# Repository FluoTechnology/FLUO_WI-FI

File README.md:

## FLUO WI-FI

[*FLUO WI-FI (V01)*](http://fluotechnology.co.uk/product/fluo-wi-fi/)

The FLUO WI-FI is the best board to to create your own IoT solution. It is a microcontroller board based on the ATmega644p 
by ATMEL (MICROCHIP) that support Arduino Ecosystem and the ESP32 module by ESPRESSIF that enables Wi-Fi and Bluetooth Low Energy (BLE).

Repository Contents
-------------------
* **/Documentation** - Data sheets, Pinout, additional product information
* **/Hardware** - EAGLE design files (.brd, .sch)
* **/Production** - Gerber files
* **/Warranty&Declaration** - Declarations documents and warranty 

License Information
-------------------

This product is _**open source**_! 

Please review the LICENSE.md file for license information. 

If you have any questions or concerns on licensing, please contact support@fluotechnology.co.uk.

Distributed as-is; no warranty is given.

  *With* :heart: *from the FLUO Team.*

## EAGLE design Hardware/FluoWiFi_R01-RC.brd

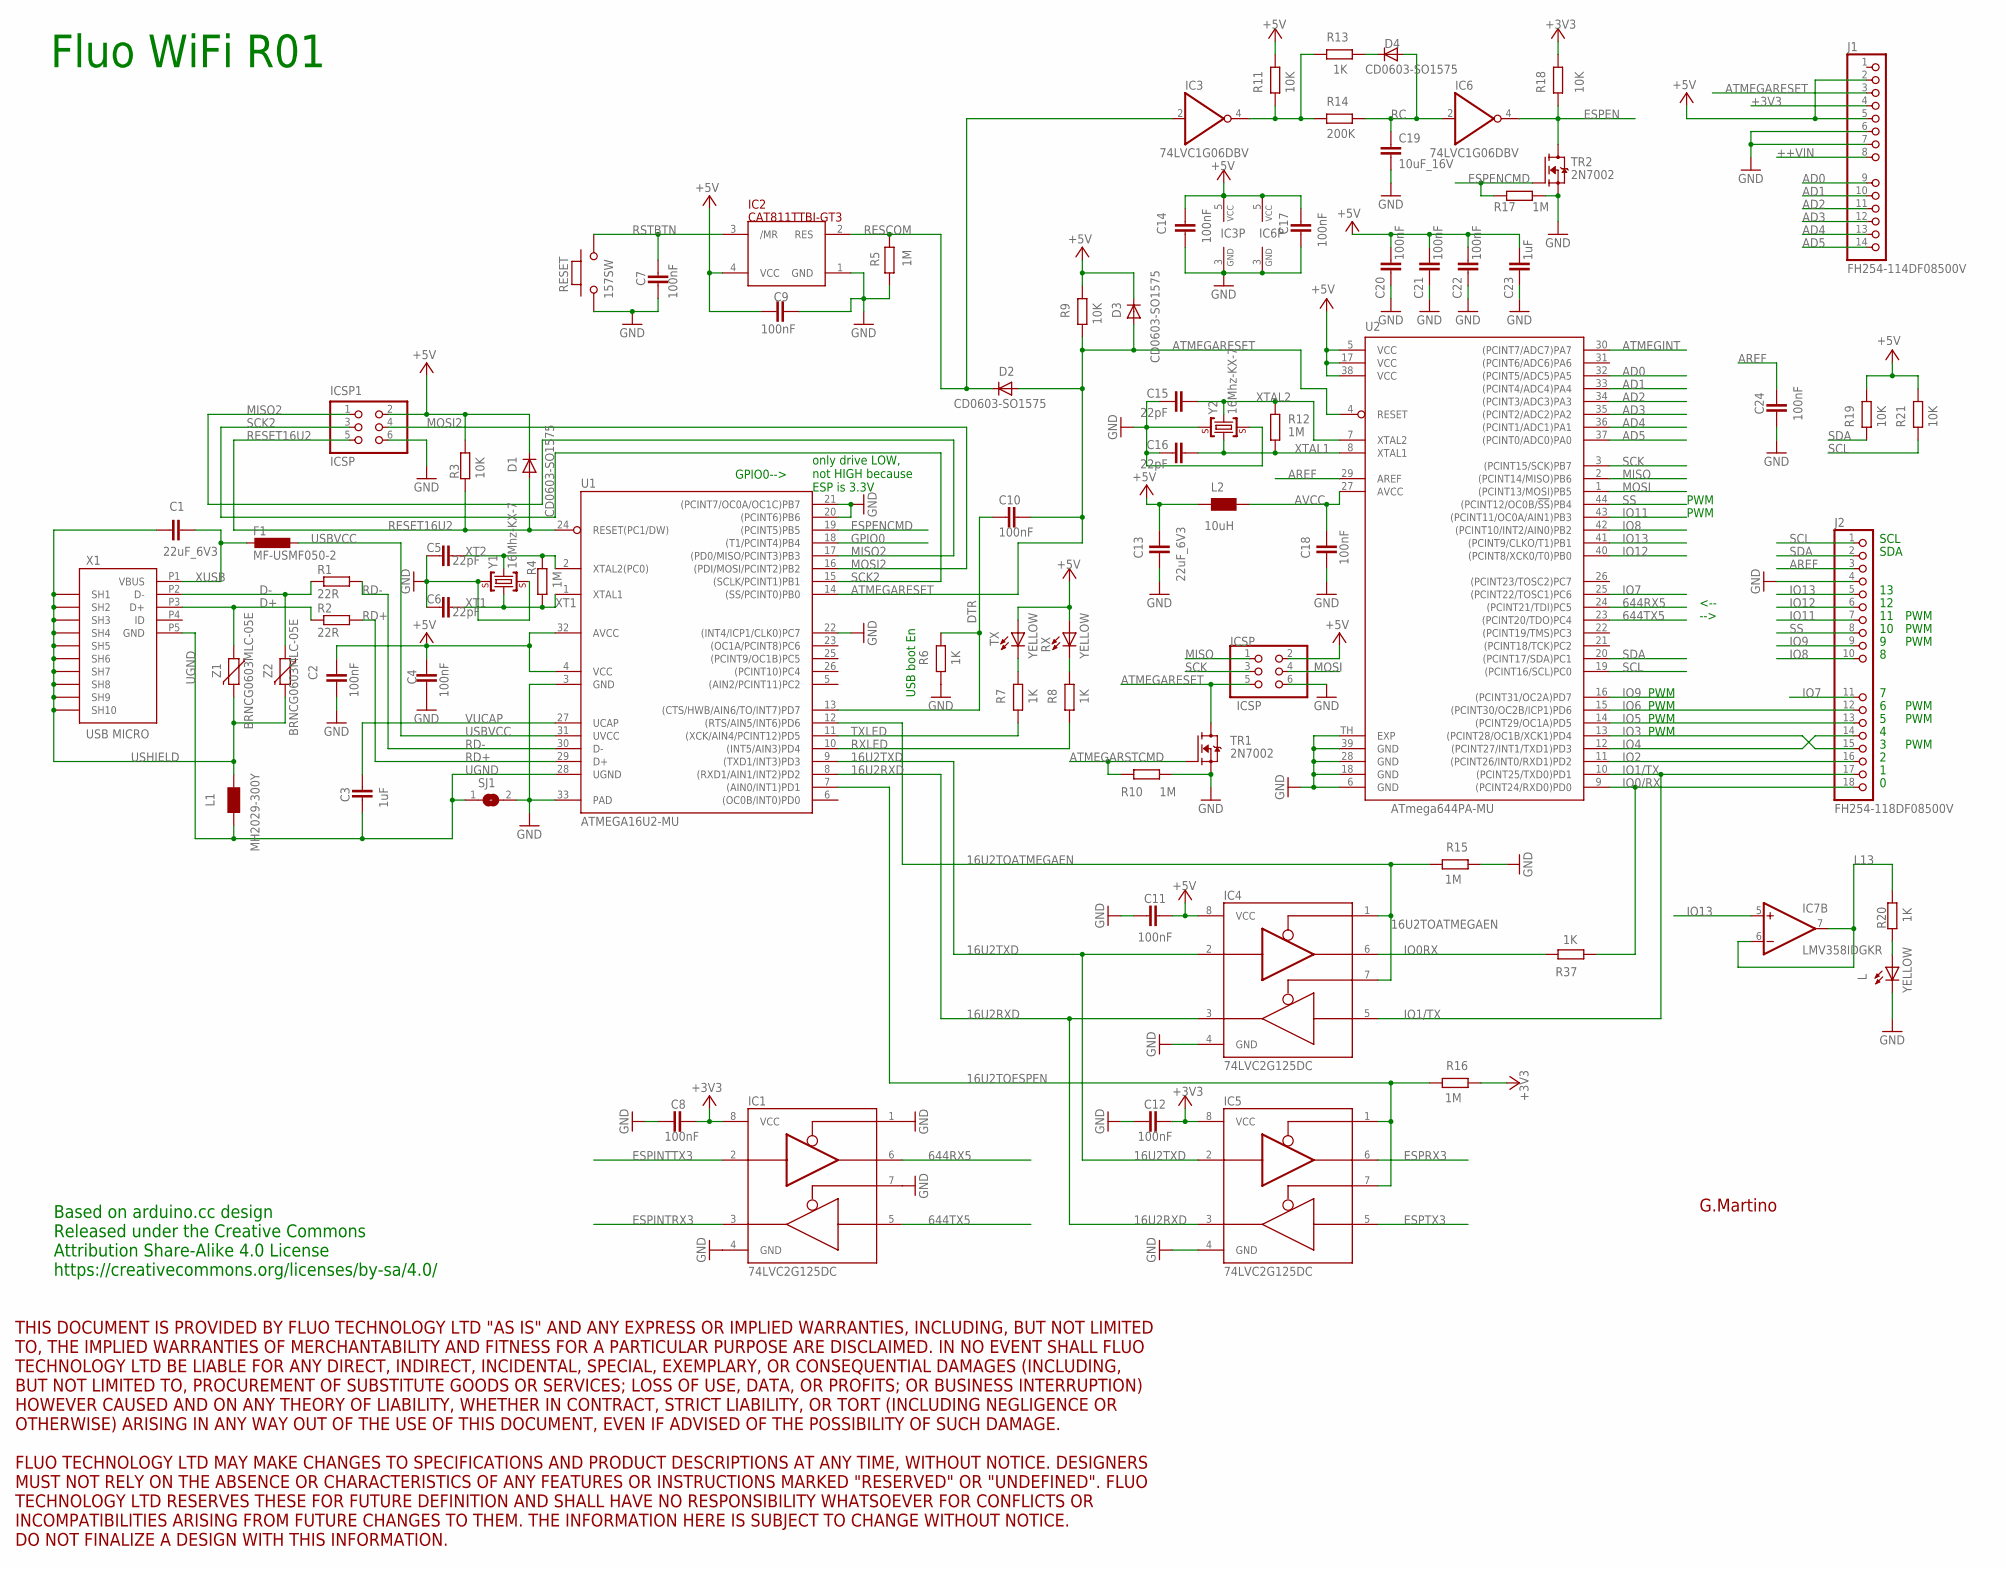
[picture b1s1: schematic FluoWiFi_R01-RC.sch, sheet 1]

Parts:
C1, C13: 22uF_6V3; C0603-ROUND
C2, C4, C7, C8, C9, C10, C11, C12, C14, C17, C18, C20, C21, C22, C24: 100nF; C0402
C3, C23: 1uF; C0402
C5, C6, C15, C16: 22pF; C0402
C19: 10uF_16V; C0805_ROUND
D1, D2, D3, D4: CD0603-SO1575; 0603
F1: MF-USMF050-2; 1210
IC1, IC4, IC5: 74LVC2G125DC; VSSOP8
IC2: CAT811TTBI-GT3; SOT143
IC3, IC6: 74LVC1G06DBV; SOT23-5
IC7: LMV358IDGKR; MSOP08
ICSP, ICSP1: ICSP; 2X03
J1: FH254-114DF08500V; 1-14-TH-PRESSFIT
J2: FH254-118DF08500V; 1X18-TH-PRESSFIT
L: YELLOW; 0402_CHIP_LED
L1: MH2029-300Y; 0805
L2: 10uH; 0805
R1, R2: 22R; R0402
R3, R9, R11, R18, R19, R21: 10K; R0402
R4, R5, R10, R12, R15, R16, R17: 1M; R0402
R6, R7, R8, R13, R20, R37: 1K; R0402
R14: 200K; R0402
RESET: 157SW; SMD_157SW
RX: YELLOW; 0402_CHIP_LED
SJ1: SJSJ_NO_RESIST; SJ_NO_RESIST
TR1, TR2: 2N7002; SOT-23
TX: YELLOW; 0402_CHIP_LED
U1: ATMEGA16U2-MU; MLF32
U2: ATmega644PA-MU; VQFN44
U$1: DISCLAIMER-FLUO
X1: USB MICRO; CON2_USB_MICRO_B_AT_HOLES
Y1, Y2: 16Mhz-KX-7; CRYSTAL-3.2-2.5
Z1, Z2: BRNCG0603MLC-05E; CT/CN0603

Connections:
16U2RXD: IC4.3 (2Y), IC5.3 (2Y), U1.8 ((RXD1/AIN1/INT2)PD2)
16U2TOATMEGAEN: IC4.1 (OE1), IC4.7 (OE2), R15.2, U1.12 ((RTS/AIN5/INT6)PD6)
16U2TOESPEN: IC5.1 (OE1), IC5.7 (OE2), R16.2, U1.7 ((AIN0/INT1)PD1)
16U2TXD: IC4.2 (1A), IC5.2 (1A), U1.9 ((TXD1/INT3)PD3)
644RX5: IC1.6 (1Y), U2.24 ((PCINT21/TDI)PC5)
644TX5: IC1.5 (2A), U2.23 ((PCINT20/TDO)PC4)
+3V3: C8.2, C12.1, IC1.8 (VCC), IC5.8 (VCC), J1.4, R16.1, R18.2; also elsewhere on the board
+5V: C2.1, C4.2, C9.1, C11.1, C13.2, C14.2, C17.2, C20.2, C21.2, C22.2, C23.1, D1.C, D3.C, IC2.4 (VCC), IC3.5 (VCC), IC4.8 (VCC), IC6.5 (VCC), ICSP.2, ICSP1.2, J1.2, J1.5, L2.1, R3.2, R9.2, R11.2, R19.2, R21.2, RX.A, TX.A, U1.4 (VCC), U1.32 (AVCC), U2.5 (VCC), U2.17 (VCC), U2.38 (VCC); also elsewhere on the board
++VIN: J1.8; also elsewhere on the board
AD0: J1.9, U2.32 ((PCINT5/ADC5)PA5)
AD1: J1.10, U2.33 ((PCINT4/ADC4)PA4)
AD2: J1.11, U2.34 ((PCINT3/ADC3)PA3)
AD3: J1.12, U2.35 ((PCINT2/ADC2)PA2)
AD4: J1.13, U2.36 ((PCINT1/ADC1)PA1)
AD5: J1.14, U2.37 ((PCINT0/ADC0)PA0)
AREF: C24.2, J2.3, U2.29 (AREF)
ATMEGARESET: C10.2, D2.A, D3.A, ICSP.5, J1.3, R9.1, TR1.3 (D), U1.14 ((SS/PCINT0)PB0), U2.4 (RESET)
ATMEGARSTCMD: R10.1, TR1.1 (G); also elsewhere on the board
ATMEGINT: U2.30 ((PCINT7/ADC7)PA7); also elsewhere on the board
AVCC: C18.2, L2.2, U2.27 (AVCC)
D+: R2.1, X1.P3 (D+), Z1.1
D-: R1.1, X1.P2 (D-), Z2.1
DTR: C10.1, R6.2, U1.13 ((CTS/HWB/AIN6/TO/INT7)PD7)
ESPEN: IC6.4 (O), R18.1, TR2.3 (D); also elsewhere on the board
ESPENCMD: R17.1, TR2.1 (G), U1.19 ((PCINT5)PB5)
ESPINTRX3: IC1.3 (2Y); also elsewhere on the board
ESPINTTX3: IC1.2 (1A); also elsewhere on the board
ESPRX3: IC5.6 (1Y); also elsewhere on the board
ESPTX3: IC5.5 (2A); also elsewhere on the board
GND: C2.2, C4.1, C5.2, C6.2, C7.1, C8.1, C9.2, C11.2, C12.2, C13.1, C14.1, C15.2, C16.2, C17.1, C18.1, C19.2, C20.1, C21.1, C22.1, C23.2, C24.1, IC1.1 (OE1), IC1.4 (GND), IC1.7 (OE2), IC2.1 (GND), IC3.3 (GND), IC4.4 (GND), IC5.4 (GND), IC6.3 (GND), ICSP.6, ICSP1.6, J1.6, J1.7, J2.4, L.C, R5.1, R6.1, R10.2, R15.1, R17.2, RESET.1, SJ1.2, TR1.2 (S), TR2.2 (S), U1.3 (GND), U1.20 ((PCINT6)PB6), U1.21 ((PCINT7/OC0A/OC1C)PB7), U1.22 ((INT4/ICP1/CLK0)PC7), U1.33 (PAD), U2.6 (GND), U2.18 (GND), U2.28 (GND), U2.39 (GND), U2.TH (EXP), Y1.2 (GND), Y1.4 (GND), Y2.2 (GND), Y2.4 (GND); also elsewhere on the board
GPIO0: U1.18 ((T1/PCINT4)PB4); also elsewhere on the board
IO0/RX: J2.18, R37.1, U2.9 ((PCINT24/RXD0)PD0)
IO0RX: IC4.6 (1Y), R37.2
IO1/TX: IC4.5 (2A), J2.17, U2.10 ((PCINT25/TXD0)PD1)
IO2: J2.16, U2.11 ((PCINT26/INT0/RXD1)PD2)
IO3: J2.15, U2.13 ((PCINT28/OC1B/XCK1)PD4)
IO4: J2.14, U2.12 ((PCINT27/INT1/TXD1)PD3)
IO5: J2.13, U2.14 ((PCINT29/OC1A)PD5)
IO6: J2.12, U2.15 ((PCINT30/OC2B/ICP1)PD6)
IO7: J2.11, U2.25 ((PCINT22/TOSC1)PC6)
IO8: J2.10, U2.42 ((PCINT10/INT2/AIN0)PB2)
IO9: J2.9, U2.16 ((PCINT31/OC2A)PD7)
IO11: J2.7, U2.43 ((PCINT11/OC0A/AIN1)PB3)
IO12: J2.6, U2.40 ((PCINT8/XCK0/T0)PB0)
IO13: IC7.5 (+IN), J2.5, U2.41 ((PCINT9/CLKO/T1)PB1)
L13: IC7.6 (-IN), IC7.7 (OUT), R20.2
MISO: ICSP.1, U2.2 ((PCINT14/MISO)PB6); also elsewhere on the board
MISO2: ICSP1.1, U1.17 ((PD0/MISO/PCINT3)PB3)
MOSI: ICSP.4, U2.1 ((PCINT13/MOSI)PB5); also elsewhere on the board
MOSI2: ICSP1.4, U1.16 ((PDI/MOSI/PCINT2)PB2)
unnamed: IC3.4 (O), R11.1, R13.1, R14.2
unnamed: D4.C, R13.2
unnamed: R7.2, TX.C
unnamed: R8.2, RX.C
unnamed: L.A, R20.1
RC: C19.1, D4.A, IC6.2 (I), R14.1
RD+: R2.2, U1.29 (D+)
RD-: R1.2, U1.30 (D-)
RESCOM: D2.C, IC2.2 (RES), IC3.2 (I), R5.2
RESET16U2: D1.A, ICSP1.5, R3.1, U1.24 (RESET(PC1/DW))
RSTBTN: C7.2, IC2.3 (/MR), RESET.2
RXLED: R8.1, U1.10 ((INT5/AIN3)PD4)
SCK: ICSP.3, U2.3 ((PCINT15/SCK)PB7); also elsewhere on the board
SCK2: ICSP1.3, U1.15 ((SCLK/PCINT1)PB1)
SCL: J2.1, R21.1, U2.19 ((PCINT16/SCL)PC0)
SDA: J2.2, R19.1, U2.20 ((PCINT17/SDA)PC1)
SS: J2.8, U2.44 ((PCINT12/OC0B/!SS!)PB4)
TXLED: R7.1, U1.11 ((XCK/AIN4/PCINT12)PD5)
UGND: C3.2, L1.1, SJ1.1, U1.28 (UGND), X1.P5 (GND)
USBVCC: F1.1, U1.31 (UVCC); also elsewhere on the board
USHIELD: C1.2, L1.2, X1.P$2 (SH7), X1.P$3 (SH8), X1.P$6 (SH9), X1.P$7 (SH10), X1.S1 (SH1), X1.S2 (SH2), X1.S3 (SH3), X1.S4 (SH4), X1.S5 (SH5), X1.S6 (SH6), Z1.2, Z2.2
VUCAP: C3.1, U1.27 (UCAP)
XT1: C6.1, R4.1, U1.1 (XTAL1), Y1.1 (C1)
XT2: C5.1, R4.2, U1.2 (XTAL2(PC0)), Y1.3 (C2)
XTAL1: C16.1, R12.1, U2.8 (XTAL1), Y2.1 (C1)
XTAL2: C15.1, R12.2, U2.7 (XTAL2), Y2.3 (C2)
XUSB: C1.1, F1.2, X1.P1 (VBUS)

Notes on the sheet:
Fluo WiFi R01
USB boot En
SDA
SCL
G.Martino
PWM
-->
<--
only drive LOW, not HIGH because ESP is 3.3V
GPIO0-->
Based on arduino.cc design Released under the Creative Commons Attribution Share-Alike 4.0 License https://creativecommons.org/licenses/by-sa/4.0/

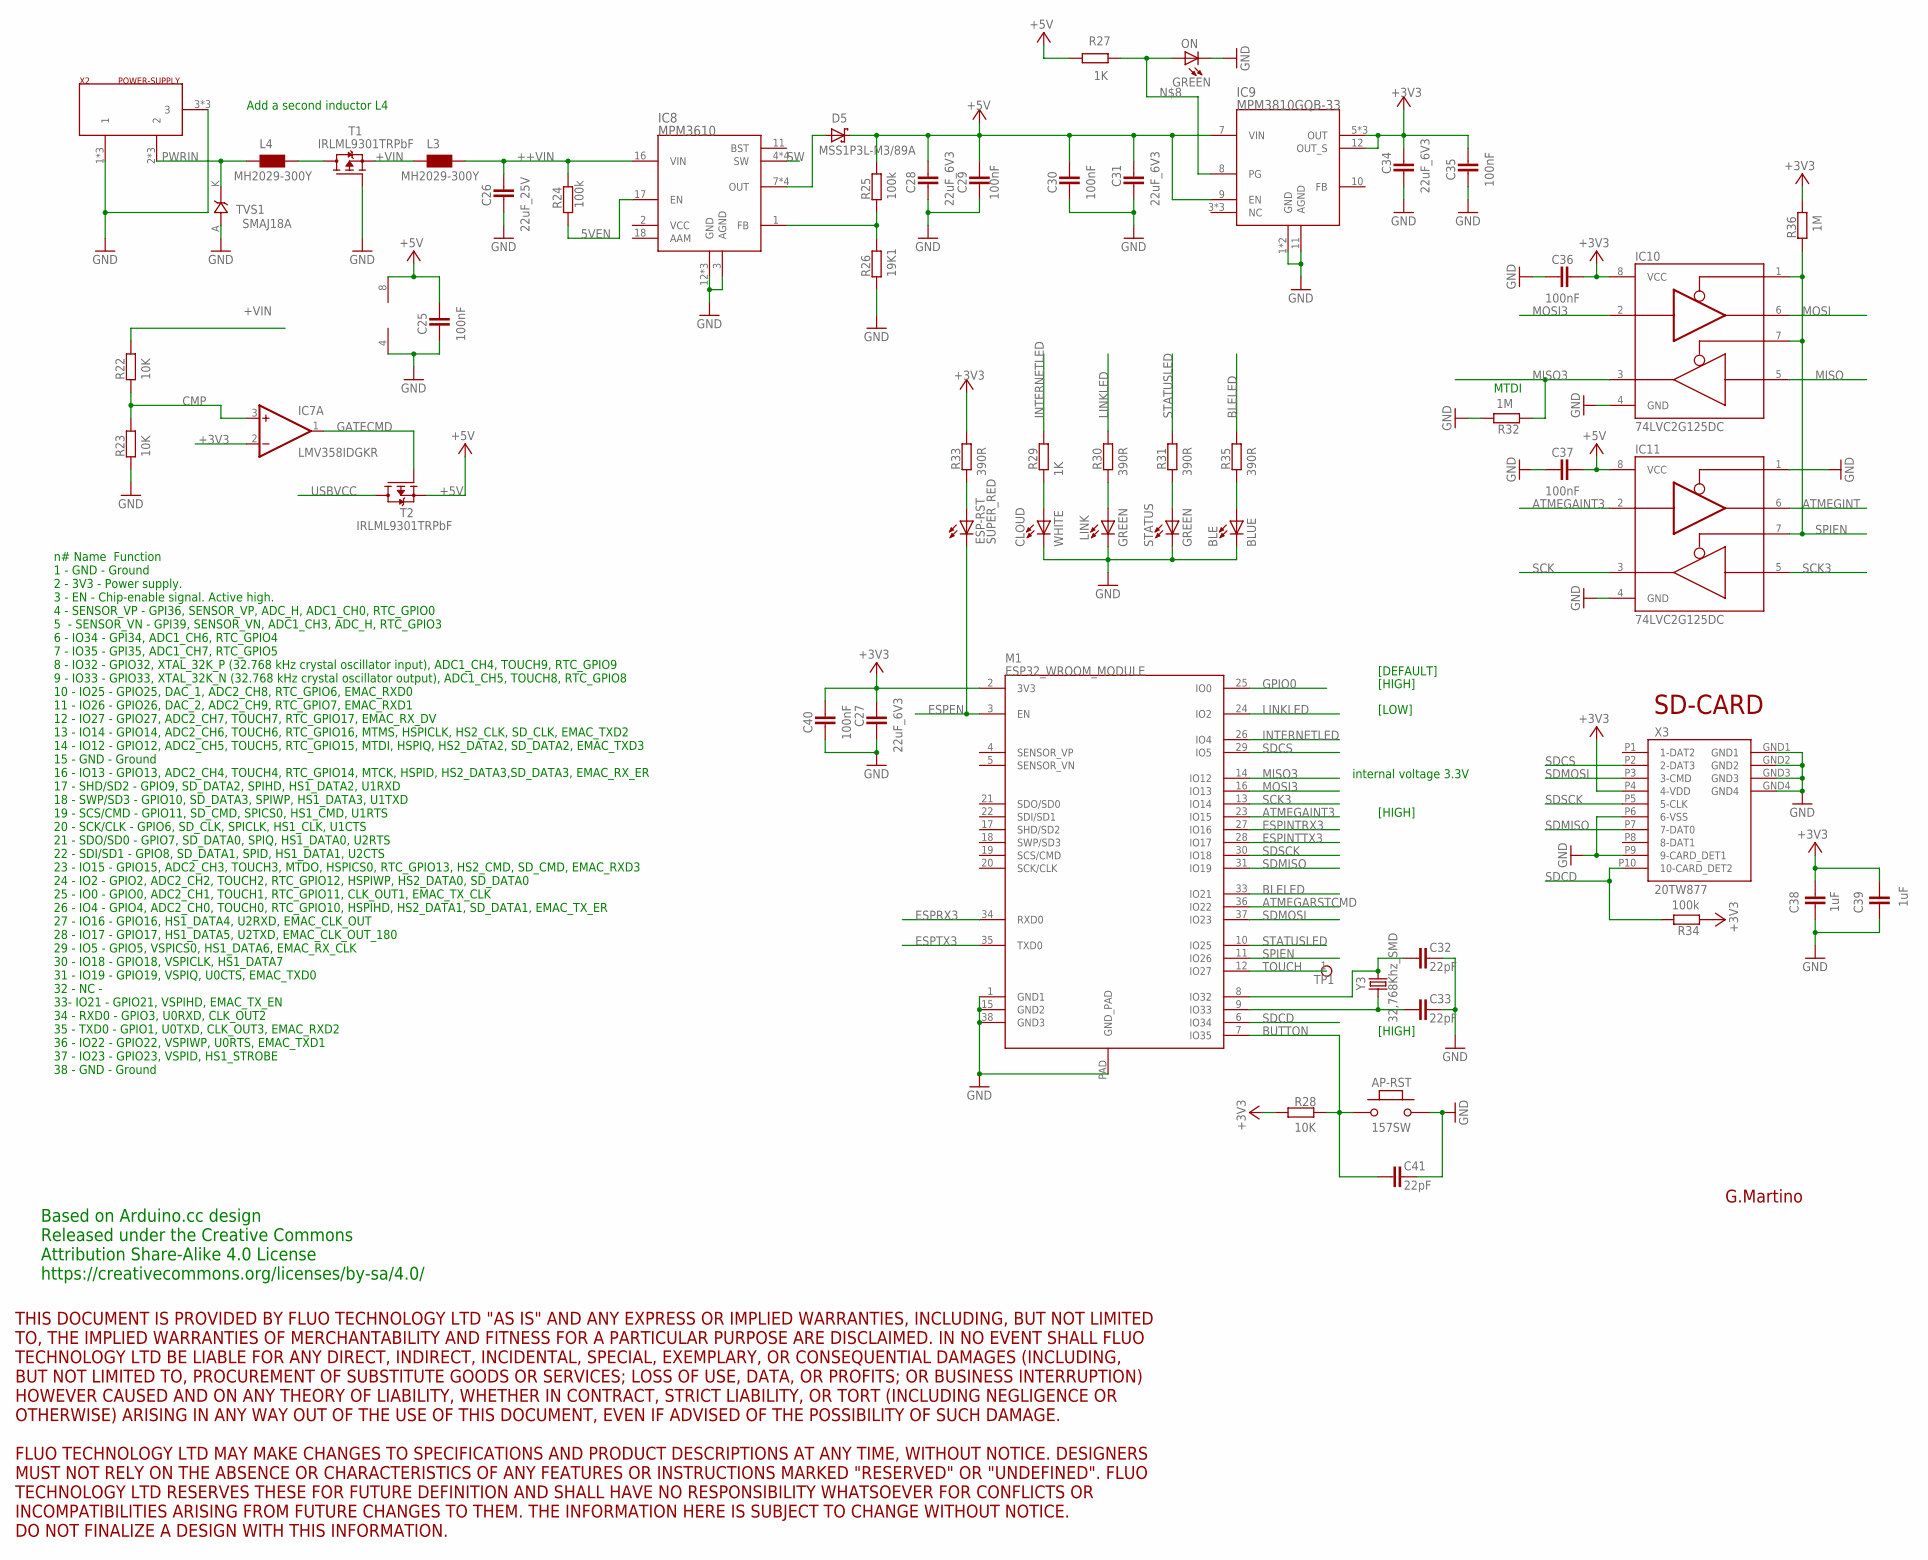
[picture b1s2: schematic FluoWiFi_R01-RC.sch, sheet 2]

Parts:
AP-RST: 157SW; SMD_157SW
BLE: BLUE; 0402_CHIP_LED
C25, C29, C30, C35, C36, C37, C40: 100nF; C0402
C26: 22uF_25V; C0805_ROUND
C27, C28, C31, C34: 22uF_6V3; C0603-ROUND
C32, C33, C41: 22pF; C0402
C38, C39: 1uF; C0402
CLOUD: WHITE; 0402_CHIP_LED
D5: MSS1P3L-M3/89A; MICROSMP
ESP-RST: SUPER_RED; 0402_CHIP_LED
IC7: LMV358IDGKR; MSOP08
IC8: MPM3610; QFN-20
IC9: MPM3810GQB-33; QFN-12
IC10, IC11: 74LVC2G125DC; VSSOP8
L3, L4: MH2029-300Y; 0805
LINK: GREEN; 0402_CHIP_LED
M1: ESP32_WROOM_MODULE; WROOM_ESP32
ON: GREEN; 0402_CHIP_LED
R22, R23, R28: 10K; R0402
R24, R25, R34: 100k; R0402
R26: 19K1; R0402
R27, R29: 1K; R0402
R30, R31, R33, R35: 390R; R0402
R32, R36: 1M; R0402
STATUS: GREEN; 0402_CHIP_LED
T1, T2: IRLML9301TRPbF; SOT-23
TP1: XXXX_TEST-POINTS_50; TEST_50
TVS1: SMAJ18A; SMA-TVS
U$2: DISCLAIMER-FLUO
X2: POWER-SUPPLY; POWERSUPPLY_DC-21MM
X3: 20TW877; 20TW877_CARD_CONNECTOR
Y3: 32,768Khz_SMD; RESONATOR_EPSON_FC_145

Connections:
5VEN: IC8.17 (EN), R24.2
+3V3: C27.1, C34.1, C35.2, C36.1, C38.2, C39.2, C40.2, IC7.2 (-IN), IC9.5 (OUT), IC9.6 (OUT), IC9.12 (OUT_S), IC9.14 (OUT), IC10.8 (VCC), M1.2 (3V3), R28.2, R33.2, R34.1, R36.1, X3.P4 (4-VDD); also elsewhere on the board
+5V: C25.2, C28.1, C29.1, C30.1, C31.1, C37.1, D5.K (C), IC7.8 (V+), IC9.7 (VIN), IC9.9 (EN), IC11.8 (VCC), R25.2, R27.2, T2.2 (S); also elsewhere on the board
+5V_SEZ: D5.A, IC8.7 (OUT), IC8.8 (OUT), IC8.9 (OUT), IC8.20 (OUT)
++VIN: C26.1, IC8.16 (VIN), L3.2, R24.1; also elsewhere on the board
+VIN: L3.1, R22.2, T1.2 (S)
ATMEGAINT3: IC11.2 (1A), M1.23 (IO15)
ATMEGARSTCMD: M1.36 (IO22); also elsewhere on the board
ATMEGINT: IC11.6 (1Y); also elsewhere on the board
BLELED: M1.33 (IO21), R35.2
BUTTON: AP-RST.1, C41.1, M1.7 (IO35), R28.1
CMP: IC7.3 (+IN), R22.1, R23.2
ESPEN: ESP-RST.C, M1.3 (EN); also elsewhere on the board
ESPINTRX3: M1.27 (IO16); also elsewhere on the board
ESPINTTX3: M1.28 (IO17); also elsewhere on the board
ESPRX3: M1.34 (RXD0); also elsewhere on the board
ESPTX3: M1.35 (TXD0); also elsewhere on the board
GATECMD: IC7.1 (OUT), T2.1 (G)
GND: AP-RST.2, BLE.C, C25.1, C26.2, C27.2, C28.2, C29.2, C30.2, C31.2, C32.2, C33.2, C34.2, C35.1, C36.2, C37.2, C38.1, C39.1, C40.1, C41.2, CLOUD.C, IC7.4 (V-), IC8.3 (AGND), IC8.12 (GND), IC8.13 (GND), IC8.14 (GND), IC9.1 (GND), IC9.2 (GND), IC9.11 (AGND), IC10.4 (GND), IC11.1 (OE1), IC11.4 (GND), LINK.C, M1.1 (GND1), M1.15 (GND2), M1.38 (GND3), M1.PAD (GND_PAD), ON.C, R23.1, R26.1, R32.1, STATUS.C, T1.1 (G), TVS1.A, X2.1, X2.3, X2.4 (1), X2.5 (1), X2.6 (3), X2.7 (3), X3.GND1, X3.GND2, X3.GND3, X3.GND4, X3.P6 (6-VSS), X3.P9 (9-CARD_DET1); also elsewhere on the board
GPIO0: M1.25 (IO0); also elsewhere on the board
INTERNETLED: M1.26 (IO4), R29.2
LINKLED: M1.24 (IO2), R30.2
MISO: IC10.5 (2A); also elsewhere on the board
MISO3: IC10.3 (2Y), M1.14 (IO12), R32.2
MOSI: IC10.6 (1Y); also elsewhere on the board
MOSI3: IC10.2 (1A), M1.16 (IO13)
unnamed: ESP-RST.A, R33.1
unnamed: L4.2, T1.3 (D)
unnamed: BLE.A, R35.1
unnamed: CLOUD.A, R29.1
unnamed: IC9.8 (PG), ON.A, R27.1
unnamed: C32.1, M1.8 (IO32), Y3.P$2 (2)
unnamed: C33.1, M1.9 (IO33), Y3.P$1 (1)
unnamed: LINK.A, R30.1
unnamed: R31.1, STATUS.A
unnamed: IC8.1 (FB), R25.1, R26.2
PWRIN: L4.1, TVS1.K, X2.2, X2.8 (2), X2.9 (2)
SCK: IC11.3 (2Y); also elsewhere on the board
SCK3: IC11.5 (2A), M1.13 (IO14)
SDCD: M1.6 (IO34), R34.2, X3.P10 (10-CARD_DET2)
SDCS: M1.29 (IO5), X3.P2 (2-DAT3)
SDMISO: M1.31 (IO19), X3.P7 (7-DAT0)
SDMOSI: M1.37 (IO23), X3.P3 (3-CMD)
SDSCK: M1.30 (IO18), X3.P5 (5-CLK)
SPIEN: IC10.1 (OE1), IC10.7 (OE2), IC11.7 (OE2), M1.11 (IO26), R36.2
STATUSLED: M1.10 (IO25), R31.2
SW: IC8.4 (SW), IC8.5 (SW), IC8.6 (SW), IC8.19 (SW)
TOUCH: M1.12 (IO27), TP1.1
USBVCC: T2.3 (D); also elsewhere on the board

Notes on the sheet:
n# Name Function 1 - GND - Ground 2 - 3V3 - Power supply. 3 - EN - Chip-enable signal. Active high. 4 - SENSOR_VP - GPI36, SENSOR_VP, ADC_H, ADC1_CH0, RTC_GPIO0 5 - SENSOR_VN - GPI39, SENSOR_VN, ADC1_CH3, ADC_H, RTC_GPIO3 6 - IO34 - GPI34, ADC1_CH6, RTC_GPIO4 7 - IO35 - GPI35, ADC1_CH7, RTC_GPIO5 8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
SD-CARD
MTDI
[HIGH]
[LOW]
internal voltage 3.3V
G.Martino
[DEFAULT]
Add a second inductor L4
Based on Arduino.cc design Released under the Creative Commons Attribution Share-Alike 4.0 License https://creativecommons.org/licenses/by-sa/4.0/

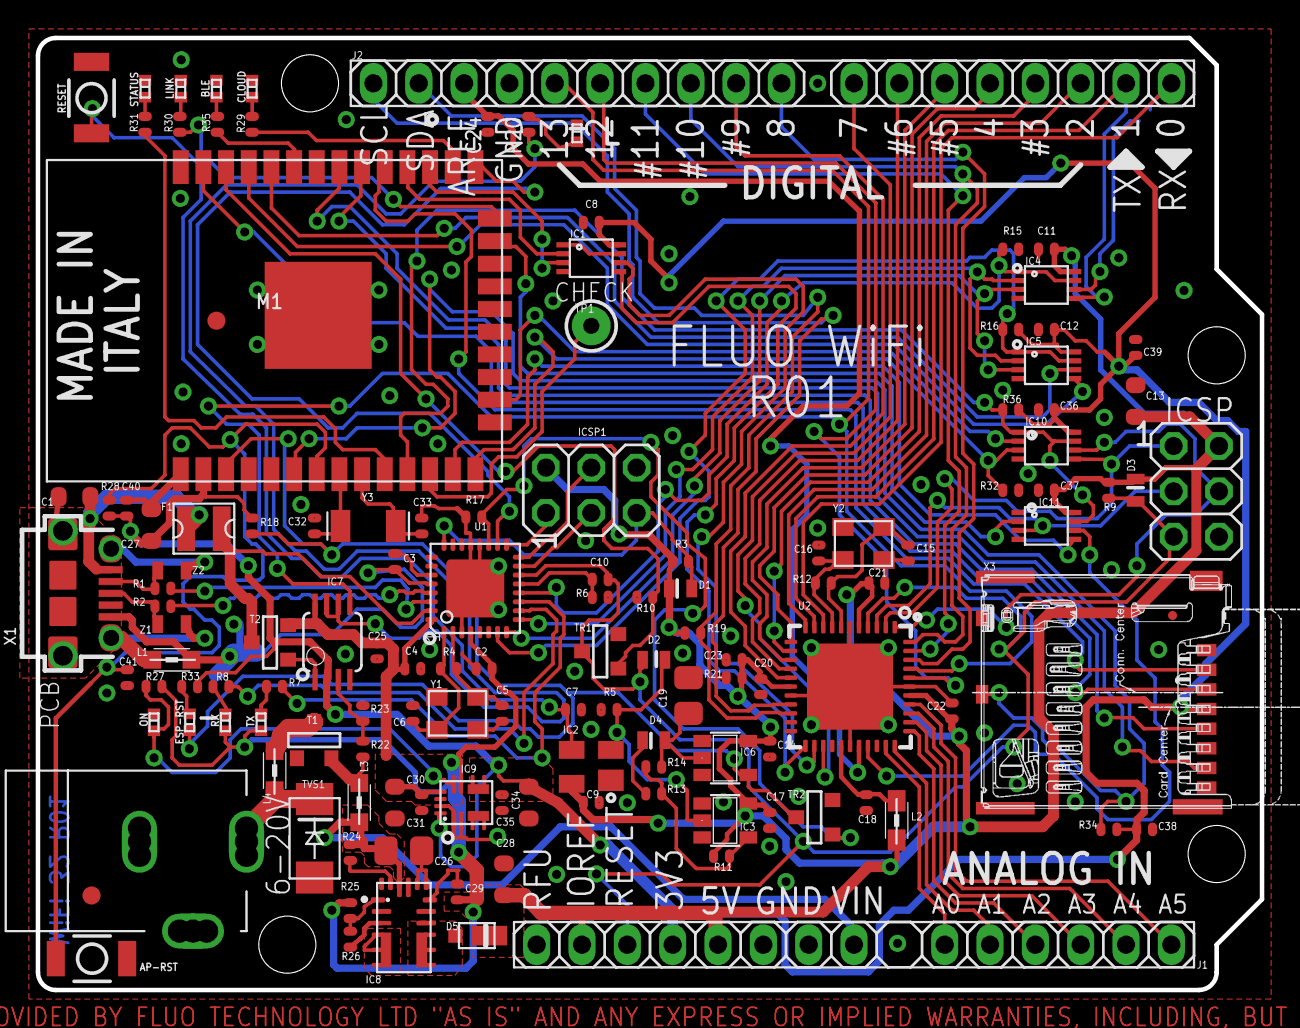
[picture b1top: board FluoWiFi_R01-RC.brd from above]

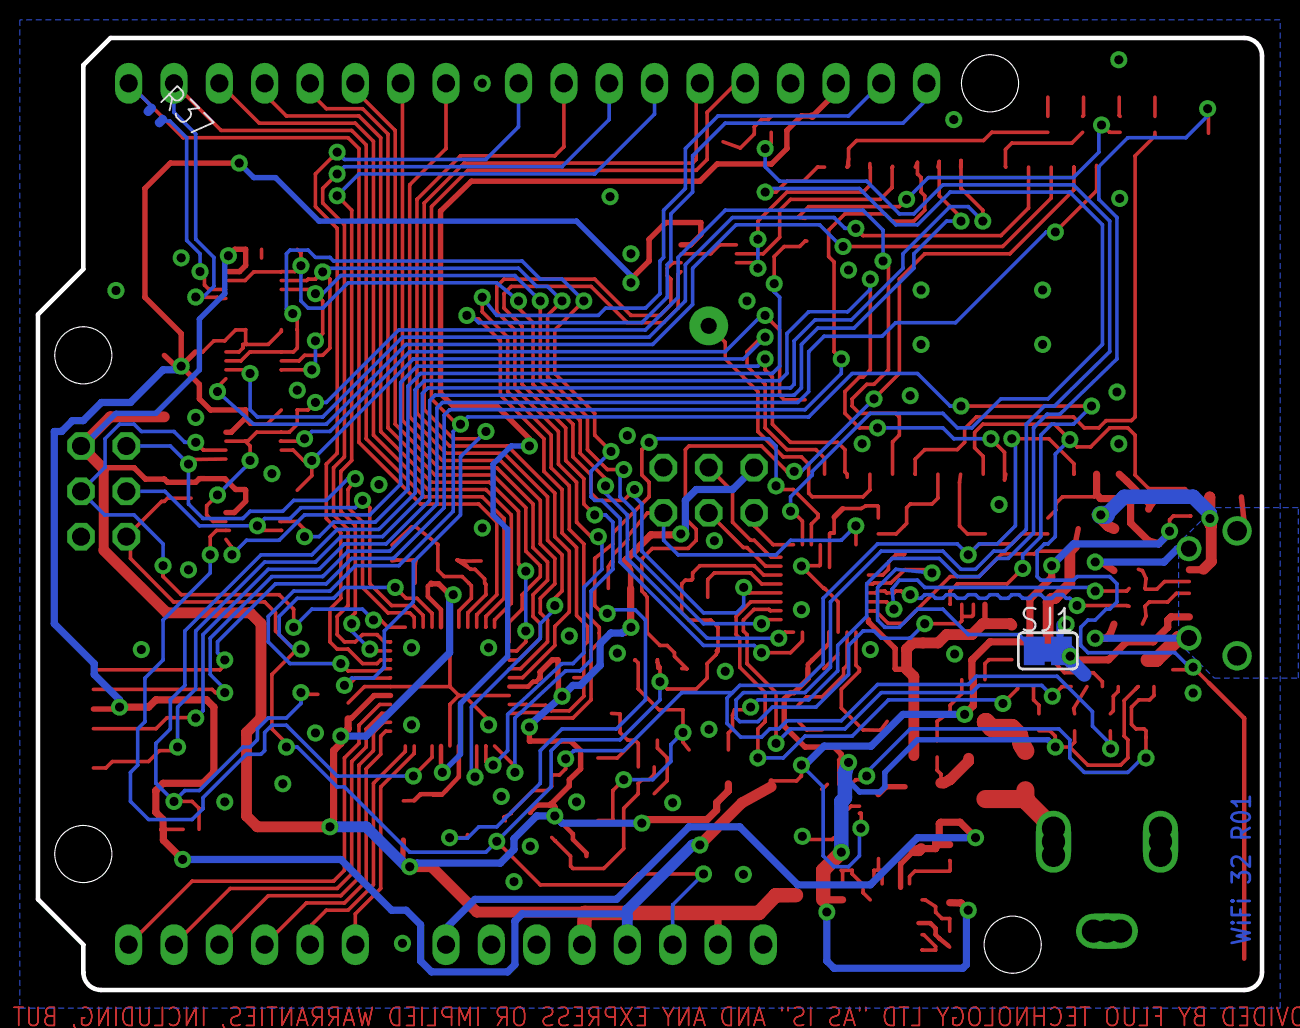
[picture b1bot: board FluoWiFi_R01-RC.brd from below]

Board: 2 copper layers, 68.6 x 53.3 mm, 138 parts (2 on the bottom side), 110 nets.

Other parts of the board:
DRILEGEND: DRILEGEND
FD1, FD3: FIDUCIALMOUNT; FIDUCIA-MOUNT
FD2: FIDUCIALMOUNT; MINI-FIDUCIAL

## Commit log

2017-12-18 First Commit, put files
